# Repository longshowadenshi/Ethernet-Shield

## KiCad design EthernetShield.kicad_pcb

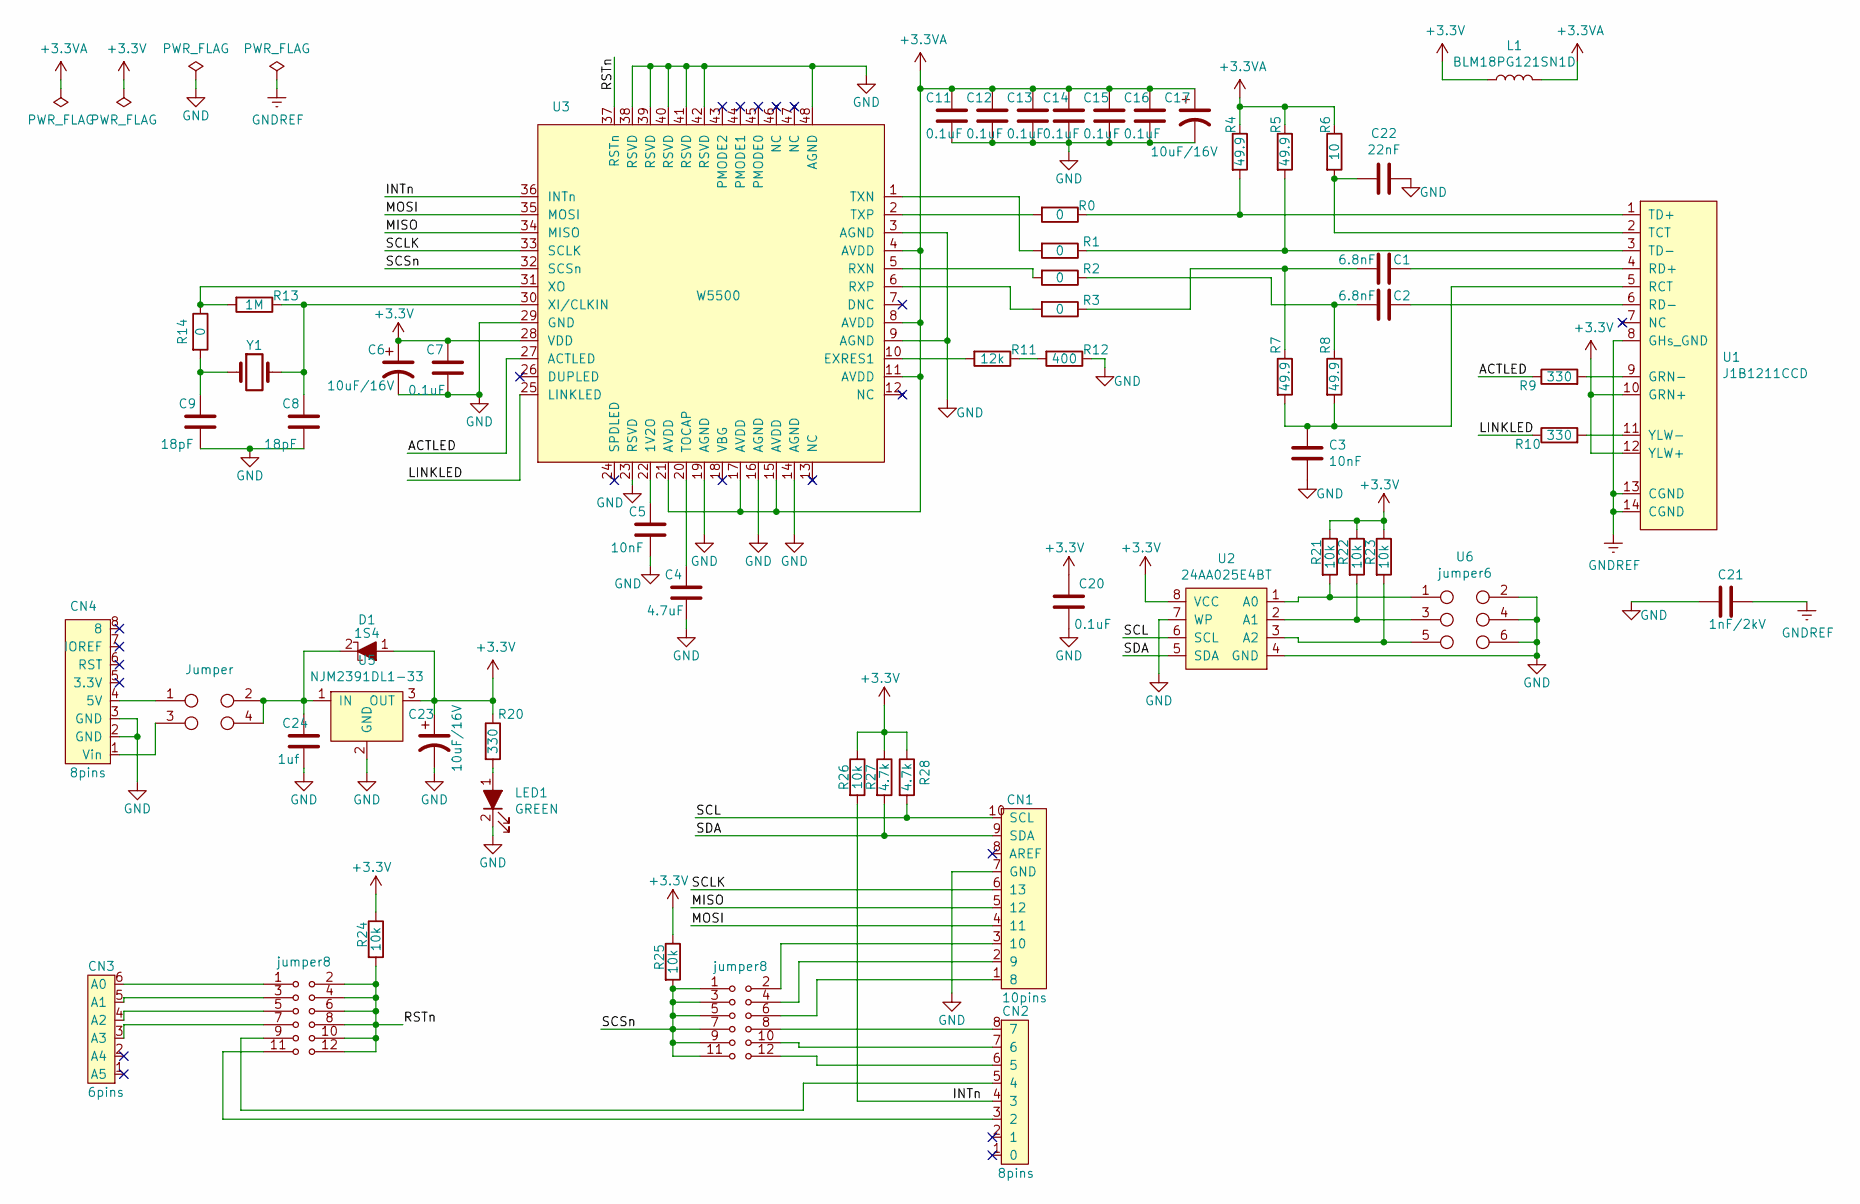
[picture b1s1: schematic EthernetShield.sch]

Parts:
C1, C2: 6.8nF; C1608C0G1H682J
C3, C5: 10nF; C1608C0G1H682J
C4: 4.7uF; C1608C0G1H682J
C6, C17, C23: 10uF/16V; 10uF-16v
C7, C11, C12, C13, C14, C15, C16, C20: 0.1uF; C0603C104Z3VACTU
C8, C9: 18pF; C1608C0G1H682J
C21: 1nF/2kV; HV1812Y102KXHATHV
C22: 22nF; C1608C0G1H682J
C24: 1uf; C1608C0G1H682J
CN1: 10pins; cn
CN2: 8pins; cn_8pins
CN3: 6pins; cn_6pins
CN4: 8pins; cn_8pins_L
D1: 1S4; 1DS4
L1: BLM18PG121SN1D; C1608C0G1H682J
LED1: GREEN; C1608C0G1H682J
R0, R1, R2, R3, R14: 0; C1608C0G1H682J
R4, R5, R7, R8: 49.9; C_1220
R6: 10; RMCF1210JT10R0
R9, R10, R20: 330; C1608C0G1H682J
R11: 12k; C_1220
R12: 400; C_1220
R13: 1M; C1608C0G1H682J
R21, R22, R23, R24, R25, R26: 10k; C1608C0G1H682J
R27, R28: 4.7k; C1608C0G1H682J
U1: J1B1211CCD
U2: 24AA025E4BT
U3: W5500; w5500
U4: Jumper; jumper
U5: NJM2391DL1-33; njm2391dl1-33
U6: jumper6
U7, U8: jumper8; jumper12
Y1: Crystal; ABM3-25MHZ-D2Y-T

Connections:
+3.3VA: C11.2, C12.2, C13.2, C14.2, C15.2, C16.2, C17.1, L1.2, R4.1, R5.1, R6.1, U3.4 (AVDD), U3.8 (AVDD), U3.11 (AVDD), U3.15 (AVDD), U3.17 (AVDD), U3.21 (AVDD)
+3V3: C6.1, C7.2, C20.2, C23.1, D1.1, L1.1, R20.1, R21.1, R22.1, R23.1, R24.1, R25.1, R26.1, R27.1, R28.1, U1.10 (GRN+), U1.12 (YLW+), U2.8 (VCC), U3.28 (VDD), U5.3 (OUT)
/ACTLED: R9.1, U3.27 (ACTLED)
/INTn: CN2.4 (3), R26.2, U3.36 (INTn)
/LINKLED: R10.1, U3.25 (LINKLED)
/MISO: CN1.5 (12), U3.34 (MISO)
/MOSI: CN1.4 (11), U3.35 (MOSI)
/RSTn: R24.2, U3.37 (RSTn), U8.2, U8.4, U8.6, U8.8, U8.10, U8.12; also elsewhere on the board
/SCL: CN1.10 (SCL), R28.2, U2.6 (SCL)
/SCLK: CN1.6 (13), U3.33 (SCLK)
/SCSn: R25.2, U3.32 (SCSn), U7.1, U7.3, U7.5, U7.7, U7.9, U7.11; also elsewhere on the board
/SDA: CN1.9 (SDA), R27.2, U2.5 (SDA)
GND: C3.1, C4.1, C5.1, C6.2, C7.1, C8.1, C9.1, C11.1, C12.1, C13.1, C14.1, C15.1, C16.1, C17.2, C20.1, C21.1, C22.1, C23.2, C24.1, CN1.7 (GND), CN4.2 (GND), CN4.3 (GND), LED1.2, R12.1, U2.4 (GND), U2.7 (WP), U3.3 (AGND), U3.9 (AGND), U3.14 (AGND), U3.16 (AGND), U3.19 (AGND), U3.23 (RSVD), U3.29 (GND), U3.38 (RSVD), U3.39 (RSVD), U3.40 (RSVD), U3.41 (RSVD), U3.42 (RSVD), U3.48 (AGND), U5.2 (GND), U6.2, U6.4, U6.6; also elsewhere on the board
GNDREF: C21.2, U1.8 (GHs_GND), U1.13 (CGND), U1.14 (CGND)
unnamed: C1.1, U1.4 (RD+)
unnamed: C1.2, R3.1, R7.1
unnamed: C2.1, U1.6 (RD-)
unnamed: C2.2, R2.1, R8.1
unnamed: C3.2, R7.2, R8.2, U1.5 (RCT)
unnamed: C4.2, U3.20 (TOCAP)
unnamed: C5.2, U3.22 (1V2O)
unnamed: C8.2, R13.1, U3.30 (XI/CLKIN), Y1.2
unnamed: C9.2, R14.2, Y1.1
unnamed: C22.2, R6.2, U1.2 (TCT)
unnamed 24: C24.2, D1.2, U4.2, U4.4, U5.1 (IN); also elsewhere on the board
unnamed 25: CN1.1 (8), U7.6; also elsewhere on the board
unnamed 26: CN1.2 (9), U7.4; also elsewhere on the board
unnamed 27: CN1.3 (10), U7.2; also elsewhere on the board
unnamed 31: CN2.3 (2), U8.11; also elsewhere on the board
unnamed 32: CN2.5 (4), U8.9; also elsewhere on the board
unnamed 33: CN2.6 (5), U7.12; also elsewhere on the board
unnamed 34: CN2.7 (6), U7.10; also elsewhere on the board
unnamed 35: CN2.8 (7), U7.8; also elsewhere on the board
unnamed 38: CN3.3 (A3), U8.7; also elsewhere on the board
unnamed 39: CN3.4 (A2), U8.5; also elsewhere on the board
unnamed 40: CN3.5 (A1), U8.3; also elsewhere on the board
unnamed 41: CN3.6 (A0), U8.1; also elsewhere on the board
unnamed 42: CN4.1 (Vin), U4.3; also elsewhere on the board
unnamed 43: CN4.4 (5V), U4.1; also elsewhere on the board
unnamed: LED1.1, R20.2
unnamed: R0.1, R4.2, U1.1 (TD+)
unnamed: R0.2, U3.2 (TXP)
unnamed: R1.1, R5.2, U1.3 (TD-)
unnamed: R1.2, U3.1 (TXN)
unnamed: R2.2, U3.5 (RXN)
unnamed: R3.2, U3.6 (RXP)
unnamed: R9.2, U1.9 (GRN-)
unnamed: R10.2, U1.11 (YLW-)
unnamed: R11.1, R12.2
unnamed: R11.2, U3.10 (EXRES1)
unnamed: R13.2, R14.1, U3.31 (XO)
unnamed 60: R21.2, U2.1 (A0), U6.1; also elsewhere on the board
unnamed 61: R22.2, U2.2 (A1), U6.3; also elsewhere on the board
unnamed 62: R23.2, U2.3 (A2), U6.5; also elsewhere on the board

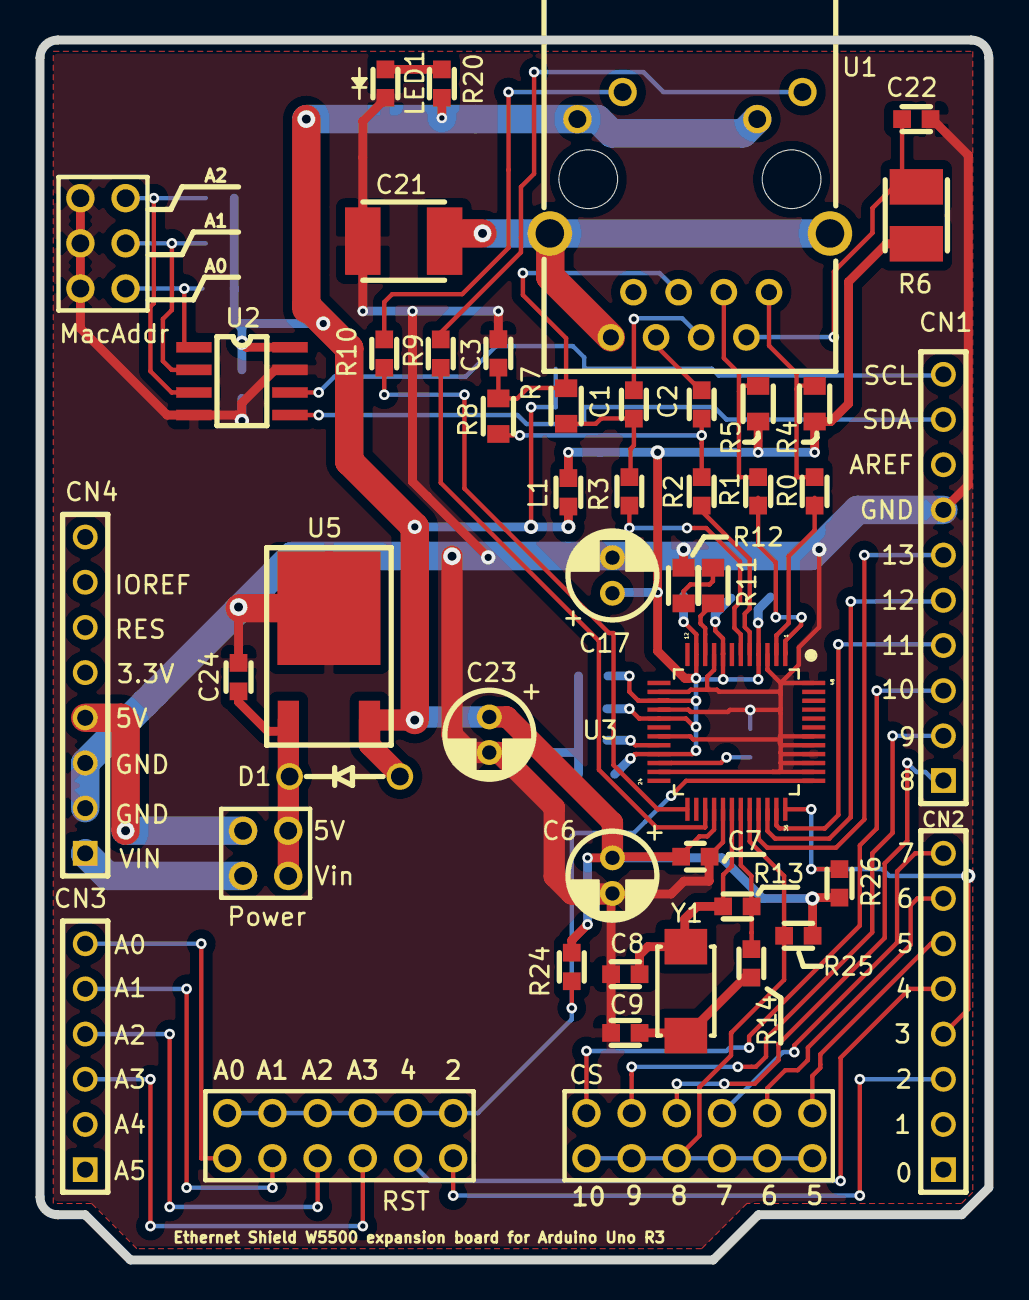
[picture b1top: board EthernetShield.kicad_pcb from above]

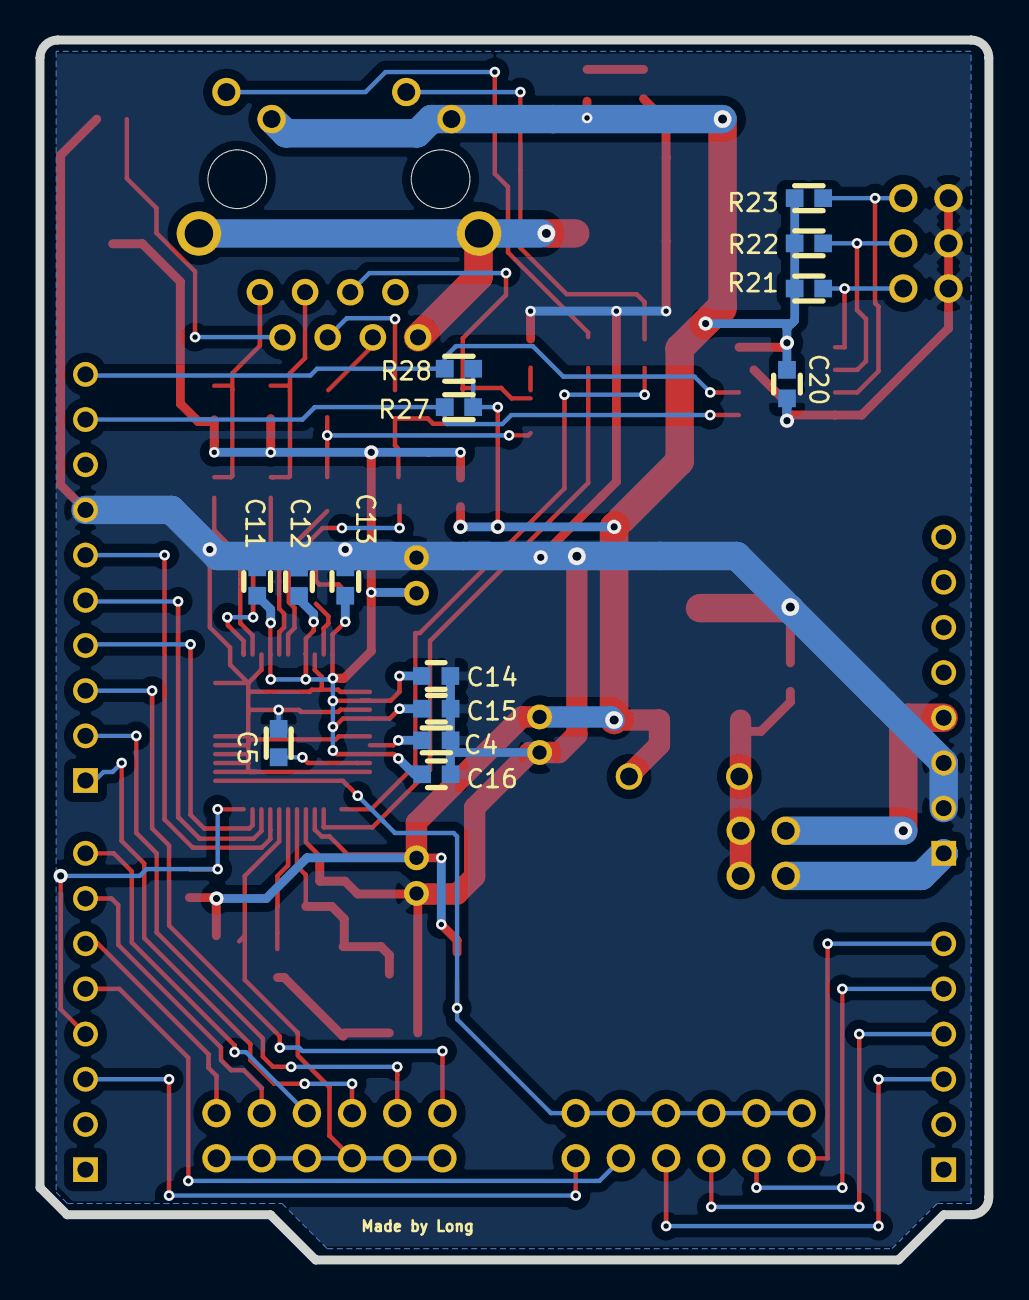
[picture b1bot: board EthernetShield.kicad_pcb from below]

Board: 2 copper layers, 53.3 x 68.6 mm, 61 parts (14 on the bottom side), 54 nets.

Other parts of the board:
CS: jumper8; jumper12
MacAddr: jumper6
Power: Jumper; jumper
RST: jumper8; jumper12

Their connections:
/RSTn: RST.2, RST.4, RST.6, RST.8, RST.10, RST.12; also elsewhere on the board
/SCSn: CS.1, CS.3, CS.5, CS.7, CS.9, CS.11; also elsewhere on the board
GND: MacAddr.2, MacAddr.4, MacAddr.6; also elsewhere on the board
unnamed 24: Power.2, Power.4; also elsewhere on the board
unnamed 25: CS.6; also elsewhere on the board
unnamed 26: CS.4; also elsewhere on the board
unnamed 27: CS.2; also elsewhere on the board
unnamed 31: RST.11; also elsewhere on the board
unnamed 32: RST.9; also elsewhere on the board
unnamed 33: CS.12; also elsewhere on the board
unnamed 34: CS.10; also elsewhere on the board
unnamed 35: CS.8; also elsewhere on the board
unnamed 38: RST.7; also elsewhere on the board
unnamed 39: RST.5; also elsewhere on the board
unnamed 40: RST.3; also elsewhere on the board
unnamed 41: RST.1; also elsewhere on the board
unnamed 42: Power.3; also elsewhere on the board
unnamed 43: Power.1; also elsewhere on the board
unnamed 60: MacAddr.1; also elsewhere on the board
unnamed 61: MacAddr.3; also elsewhere on the board
unnamed 62: MacAddr.5; also elsewhere on the board
